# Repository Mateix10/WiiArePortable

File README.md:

# WiiArePortable

This is a work in progress custom board for a portable wii.

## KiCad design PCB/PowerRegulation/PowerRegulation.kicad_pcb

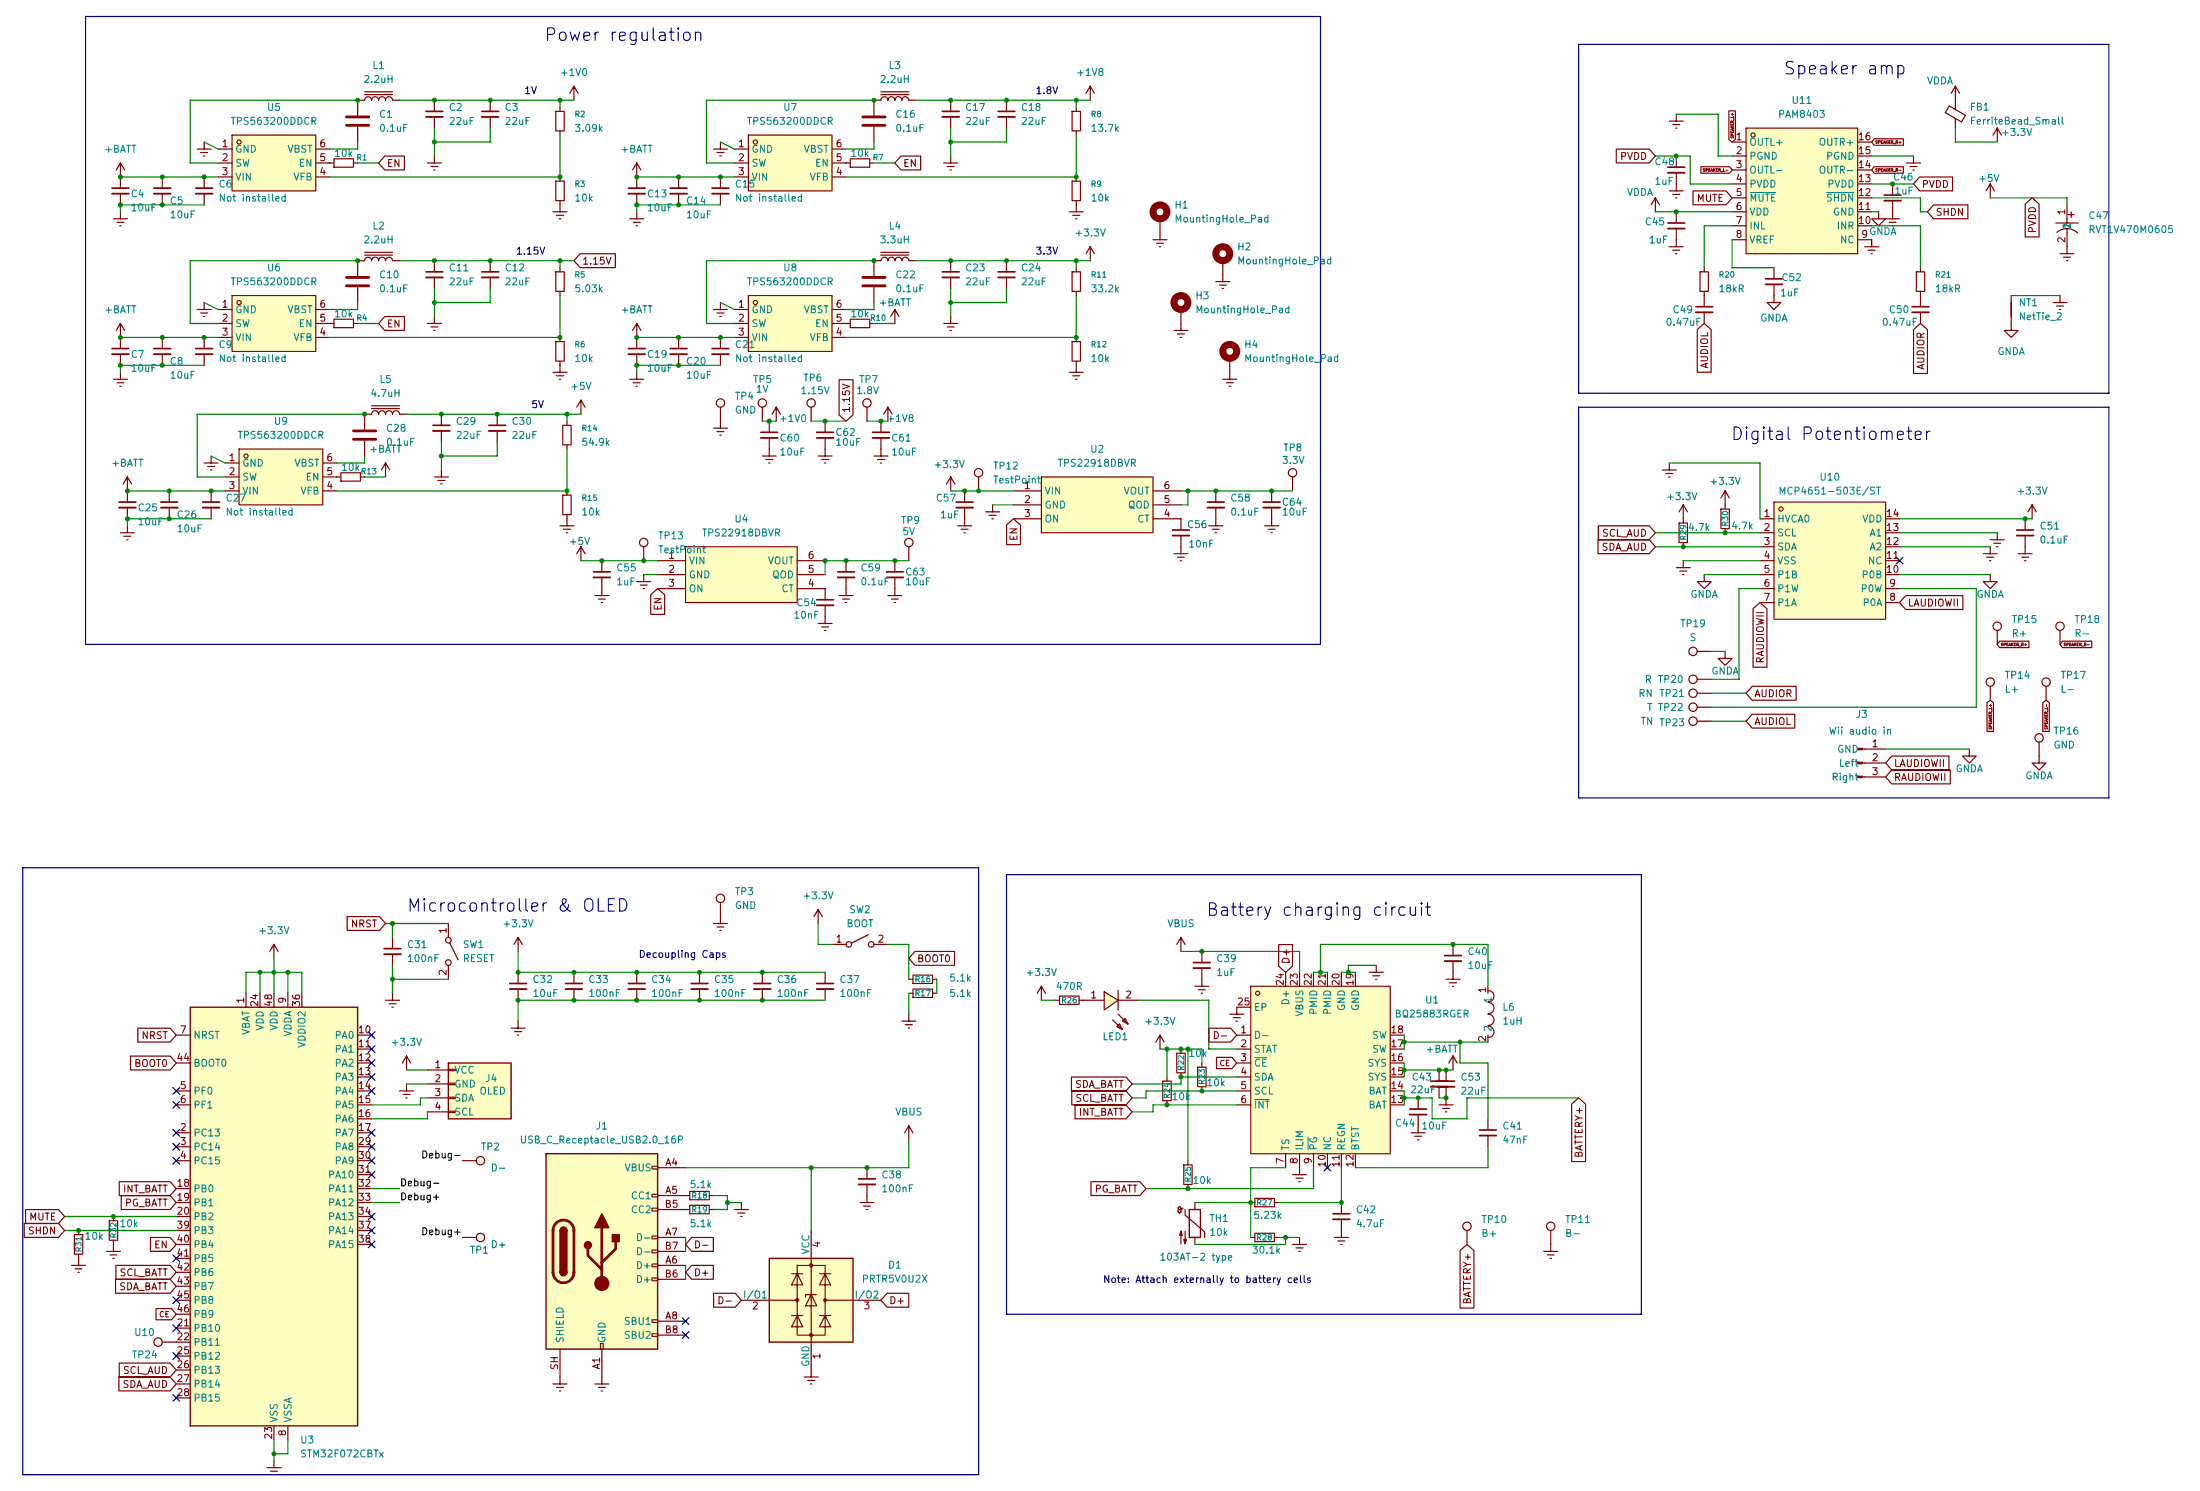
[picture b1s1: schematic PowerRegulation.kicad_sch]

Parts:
C1, C10, C16, C22, C28, C51: 0.1uF; R0603; LCSC Part C1590
C2, C3, C11, C12, C17, C18, C23, C24, C29, C30, C43, C53: 22uF; R1206; LCSC Part C5672
C4, C5, C7, C8, C13, C14, C19, C20, C25, C26, C32, C40, C44, C60, C61, C62, C63, C64: 10uF; R0805; LCSC Part C1713
C6, C9, C15, C21, C27: Not installed; R0805
C31, C33, C34, C35, C36, C37, C38: 100nF; R0603; LCSC Part C1713
C39, C45, C46, C48, C52: 1uF; R0603; LCSC Part C1592
C41: 47nF; R0603; LCSC Part C1622
C42: 4.7uF; R0805; LCSC Part C1779
C47: RVT1V470M0605; CAP-SMD_BD6.3-L6.6-W6.6-LS7.2-FD; MPN RVT1V470M0605; LCSC Part C3344
C49, C50: 0.47uF; R0603; LCSC Part C1623
C54, C56: 10nF; R1206; LCSC Part C1846
C55, C57: 1uF; R1206; LCSC Part C1848
C58, C59: 0.1uF; R1206; LCSC Part C1848
D1: PRTR5V0U2X; SOT-143; LCSC Part C5158049
FB1: FerriteBead_Small; R0805; LCSC Part C1017
H1, H2, H3, H4: MountingHole_Pad; MountingHole_3.2mm_M3_Pad_Via
J1: USB_C_Receptacle_USB2.0_16P; USB_C_Receptacle_Palconn_UTC16-G
J3: Wii audio in; PinHeader_1x03_P2.54mm_Vertical
J4: OLED; PinHeader_1x04_P2.54mm_Vertical
L1, L2, L3: 2.2uH; IND-SMD_L4.5-W4.1_SRP4020TA; LCSC Part C237985
L4: 3.3uH; IND-SMD_L5.7-W5.2; LCSC Part C189931
L5: 4.7uH; IND-SMD_L7.1-W6.6; LCSC Part C216191
L6: 1uH; IND-SMD_L5.4-W5.2_PSPMAA0503; MPN PSPMAA0503-1R0M-ANP; LCSC Part C436531
LED1: BL-HJC36G-AV-TRB; LED0603-R-RD_AMBER; MPN BL-HJC36G-AV-TRB; LCSC Part C165983
NT1: NetTie_2; NetTie-2_SMD_Pad2.0mm
R1, R3, R4, R6, R7, R9, R10, R12, R13, R15, R22, R23, R24, R25, R31, R32: 10k; R1206; LCSC Part C1489
R2: 3.09k; R0603; LCSC Part C4211
R5: 5.03k; R0603; LCSC Part C166926
R8: 13.7k; R0603; LCSC Part C22793
R11: 33.2k; R0805; LCSC Part C37252
R14: 54.9k; R0603; LCSC Part C23077
R16, R17, R18, R19: 5.1k; R0603; LCSC Part C23186
R20, R21: 18kR; R0805; LCSC Part C17506
R26: 470R; R0805; LCSC Part C436531
R27: 5.23k; R0603; LCSC Part C23068
R28: 30.1k; R1206; LCSC Part C48533691
R29, R30: 4.7k; R0805; LCSC Part C17673
SW1: RESET; SW_SPST_EVQPE1
SW2: BOOT; SW_SPST_EVQPE1
TH1: 10k; R1206; LCSC Part C1489
TP1: D+; TestPoint_Pad_D2.0mm
TP2: D-; TestPoint_Pad_D2.0mm
TP3: GND; TestPoint_Pad_D2.0mm
TP4: GND; TestPoint_Pad_D4.0mm
TP5: 1V; TestPoint_Pad_D4.0mm
TP6: 1.15V; TestPoint_Pad_D4.0mm
TP7: 1.8V; TestPoint_Pad_D4.0mm
TP8: 3.3V; TestPoint_Pad_D4.0mm
TP9: 5V; TestPoint_Pad_D4.0mm
TP10: B+; TestPoint_Pad_D4.0mm
TP11: B-; TestPoint_Pad_D4.0mm
TP12, TP13: TestPoint; TestPoint_Pad_D1.0mm
TP14: L+; TestPoint_Pad_D2.5mm
TP15: R+; TestPoint_Pad_D2.5mm
TP16: GND; TestPoint_Pad_D2.5mm
TP17: L-; TestPoint_Pad_D2.5mm
TP18: R-; TestPoint_Pad_D2.5mm
TP19: S; TestPoint_Pad_D2.0mm
TP20: R; TestPoint_Pad_D2.0mm
TP21: RN; TestPoint_Pad_D2.0mm
TP22: T; TestPoint_Pad_D2.0mm
TP23: TN; TestPoint_Pad_D2.0mm
TP24: U10; TestPoint_Pad_D2.0mm
U1: BQ25883RGER; VFQFPN-24_L4.0-W4.0-P0.50-BL-EP2.8; MPN BQ25883RGER; LCSC Part C544362
U2, U4: TPS22918DBVR; SOT-23-6_L2.9-W1.6-P0.95-LS2.8-BR; MPN TPS22918DBVR; LCSC Part C131941
U3: STM32F072CBTx; LQFP-48_L7.0-W7.0-P0.50-LS9.0-BL; LCSC Part C81720
U5, U6, U7, U8, U9: TPS563200DDCR; SOT-23-6_L2.9-W1.6-P0.95-LS2.8-BR; MPN TPS563200DDCR; LCSC Part C97253
U10: MCP4651-503E/ST; TSSOP-14_L5.0-W4.4-P0.65-LS6.4-BL; MPN MCP4651-503E/ST; LCSC Part C148010
U11: PAM8403; SOP-16_L10.0-W3.9-P1.27-LS6.0-BL; MPN PAM8403; LCSC Part C5122557

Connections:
1.15V: C11.1, C12.1, C62.1, L2.2, R5.1, TP6.1 (1_1)
+1V0: C2.1, C3.1, C60.1, L1.2, R2.1, TP5.1 (1_1)
+1V8: C17.1, C18.1, C61.1, L3.2, R8.1, TP7.1 (1_1)
+3.3V: C23.1, C24.1, C32.1, C33.1, C34.1, C35.1, C36.1, C37.1, C51.1, C57.1, FB1.2, J4.1 (VCC), L4.2, R11.1, R22.1, R23.1, R24.1, R25.1, R26.1, R29.1, R30.1, SW2.1 (A), TP12.1 (1_1), U2.1 (VIN), U3.1 (VBAT), U3.9 (VDDA), U3.24 (VDD), U3.36 (VDDIO2), U3.48 (VDD), U10.14 (VDD)
+BATT: C4.1, C5.1, C6.1, C7.1, C8.1, C9.1, C13.1, C14.1, C15.1, C19.1, C20.1, C21.1, C25.1, C26.1, C27.1, C43.1, C53.1, R10.2, R13.2, U1.15 (SYS), U1.16 (SYS), U5.3 (VIN), U6.3 (VIN), U7.3 (VIN), U8.3 (VIN), U9.3 (VIN)
/Debug+: TP1.1 (1_1), U3.33 (PA12)
/Debug-: TP2.1 (1_1), U3.32 (PA11)
AUDIOL: C49.2, TP23.1 (1_1)
AUDIOR: C50.2, TP21.1 (1_1)
BATTERY+: C44.1, TP10.1 (1_1), U1.13 (BAT), U1.14 (BAT)
BOOT0: R16.1, SW2.2 (B), U3.44 (BOOT0)
CE: U1.3 (~CE), U3.46 (PB9)
D+: D1.3 (I/O2), J1.A6 (D+), J1.B6 (D+), U1.24 (D+)
D-: D1.2 (I/O1), J1.A7 (D-), J1.B7 (D-), U1.1 (D-)
EN: R1.2, R4.2, R7.2, U2.3 (ON), U3.40 (PB4), U4.3 (ON)
GNDA: C52.2, J3.1 (GND), NT1.1, TP16.1 (1_1), TP19.1 (1_1), U10.5 (P1B), U10.10 (P0B), U11.11 (GND)
GNDREF: C2.2, C3.2, C4.2, C5.2, C6.2, C7.2, C8.2, C9.2, C11.2, C12.2, C13.2, C14.2, C15.2, C17.2, C18.2, C19.2, C20.2, C21.2, C23.2, C24.2, C25.2, C26.2, C27.2, C29.2, C30.2, C31.2, C32.2, C33.2, C34.2, C35.2, C36.2, C37.2, C38.2, C39.2, C40.2, C42.2, C43.2, C44.2, C45.2, C46.2, C47.2, C48.2, C51.2, C53.2, C54.2, C55.2, C56.2, C57.2, C58.2, C59.2, C60.2, C61.2, C62.2, C63.2, C64.2, D1.1 (GND), H1.1 (1_1), H2.1 (1_1), H3.1 (1_1), H4.1 (1_1), J1.A1 (GND), J1.A12 (GND), J1.B1 (GND), J1.B12 (GND), J1.SH (SHIELD), J4.2 (GND), NT1.2, R3.2, R6.2, R9.2, R12.2, R15.2, R17.1, R18.2, R19.2, R28.2, R31.2, R32.2, SW1.2 (B), TH1.2, TP3.1 (1_1), TP4.1 (1_1), TP11.1 (1_1), U1.8 (ILIM), U1.19 (GND), U1.20 (GND), U1.25 (EP), U2.2 (GND), U3.8 (VSSA), U3.23 (VSS), U3.35 (VSS), U3.47 (VSS), U4.2 (GND), U5.1 (GND), U6.1 (GND), U7.1 (GND), U8.1 (GND), U9.1 (GND), U10.1 (HVCA0), U10.4 (VSS), U10.12 (A2), U10.13 (A1), U11.2 (PGND), U11.9 (NC), U11.15 (PGND)
INT_BATT: R24.2, U1.6 (~INT), U3.18 (PB0)
LAUDIOWII: J3.2 (Left), U10.8 (P0A)
MUTE: R32.1, U3.20 (PB2), U11.5 (~MUTE)
NRST: C31.1, SW1.1 (A), U3.7 (NRST)
unnamed: C40.1, L6.1, U1.21 (PMID), U1.22 (PMID)
unnamed: C41.1, L6.2, U1.17 (SW), U1.18 (SW)
unnamed: C49.1, R20.2
unnamed: C50.1, R21.2
unnamed: J1.A5 (CC1), R18.1
unnamed: J1.B5 (CC2), R19.1
unnamed: J4.4 (SCL), U3.16 (PA6)
unnamed: J4.3 (SDA), U3.15 (PA5)
unnamed: LED1.1 (A), R26.2
unnamed: LED1.2 (C), U1.2 (STAT)
unnamed: R16.2, R17.2
unnamed: C41.2, U1.12 (BTST)
unnamed: C42.1, R27.2, U1.11 (REGN)
unnamed: R27.1, R28.1, TH1.1, U1.7 (TS)
unnamed: C56.1, U2.4 (CT)
unnamed: C58.1, C64.1, TP8.1 (1_1), U2.5 (QOD), U2.6 (VOUT)
unnamed: TP24.1 (1_1), U3.22 (PB11)
unnamed: C54.1, U4.4 (CT)
unnamed: C59.1, C63.1, TP9.1 (1_1), U4.5 (QOD), U4.6 (VOUT)
unnamed: R1.1, U5.5 (EN)
unnamed: C1.1, L1.1, U5.2 (SW)
unnamed: C1.2, U5.6 (VBST)
unnamed: R2.2, R3.1, U5.4 (VFB)
unnamed: R4.1, U6.5 (EN)
unnamed: C10.1, L2.1, U6.2 (SW)
unnamed: C10.2, U6.6 (VBST)
unnamed: R5.2, R6.1, U6.4 (VFB)
unnamed: R7.1, U7.5 (EN)
unnamed: C16.1, L3.1, U7.2 (SW)
unnamed: C16.2, U7.6 (VBST)
unnamed: R8.2, R9.1, U7.4 (VFB)
unnamed: R10.1, U8.5 (EN)
unnamed: C22.1, L4.1, U8.2 (SW)
unnamed: C22.2, U8.6 (VBST)
unnamed: R11.2, R12.1, U8.4 (VFB)
unnamed: R13.1, U9.5 (EN)
unnamed: C28.1, L5.1, U9.2 (SW)
unnamed: C28.2, U9.6 (VBST)
unnamed: R14.2, R15.1, U9.4 (VFB)
unnamed: TP22.1 (1_1), U10.9 (P0W)
unnamed: TP20.1 (1_1), U10.6 (P1W)
unnamed: R20.1, U11.7 (INL)
unnamed: R21.1, U11.10 (INR)
unnamed: C52.1, U11.8 (VREF)
PG_BATT: R25.2, U1.9 (~PG), U3.19 (PB1)
PVDD: C29.1, C30.1, C46.1, C47.1, C48.1, C55.1, L5.2, R14.1, TP13.1 (1_1), U4.1 (VIN), U11.4 (PVDD), U11.13 (PVDD)
RAUDIOWII: J3.3 (Right), U10.7 (P1A)
SCL_AUD: R30.2, U3.26 (PB13), U10.2 (SCL)
SCL_BATT: R23.2, U1.5 (SCL), U3.42 (PB6)
SDA_AUD: R29.2, U3.27 (PB14), U10.3 (SDA)
SDA_BATT: R22.2, U1.4 (SDA), U3.43 (PB7)
SHDN: R31.1, U3.39 (PB3), U11.12 (~SHDN)
SPEAKER_L+: TP14.1 (1_1), U11.1 (OUTL+)
SPEAKER_L-: TP17.1 (1_1), U11.3 (OUTL-)
SPEAKER_R+: TP15.1 (1_1), U11.16 (OUTR+)
SPEAKER_R-: TP18.1 (1_1), U11.14 (OUTR-)
VBUS: C38.1, C39.1, D1.4 (VCC), J1.A4 (VBUS), J1.A9 (VBUS), J1.B4 (VBUS), J1.B9 (VBUS), U1.23 (VBUS)
VDDA: C45.1, FB1.1, U11.6 (VDD)

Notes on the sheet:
Digital Potentiometer
3.3V
Decoupling Caps
Note: Attach externally to battery cells
1.8V
Microcontroller & OLED
Power regulation
Battery charging circuit
1.15V
Speaker amp

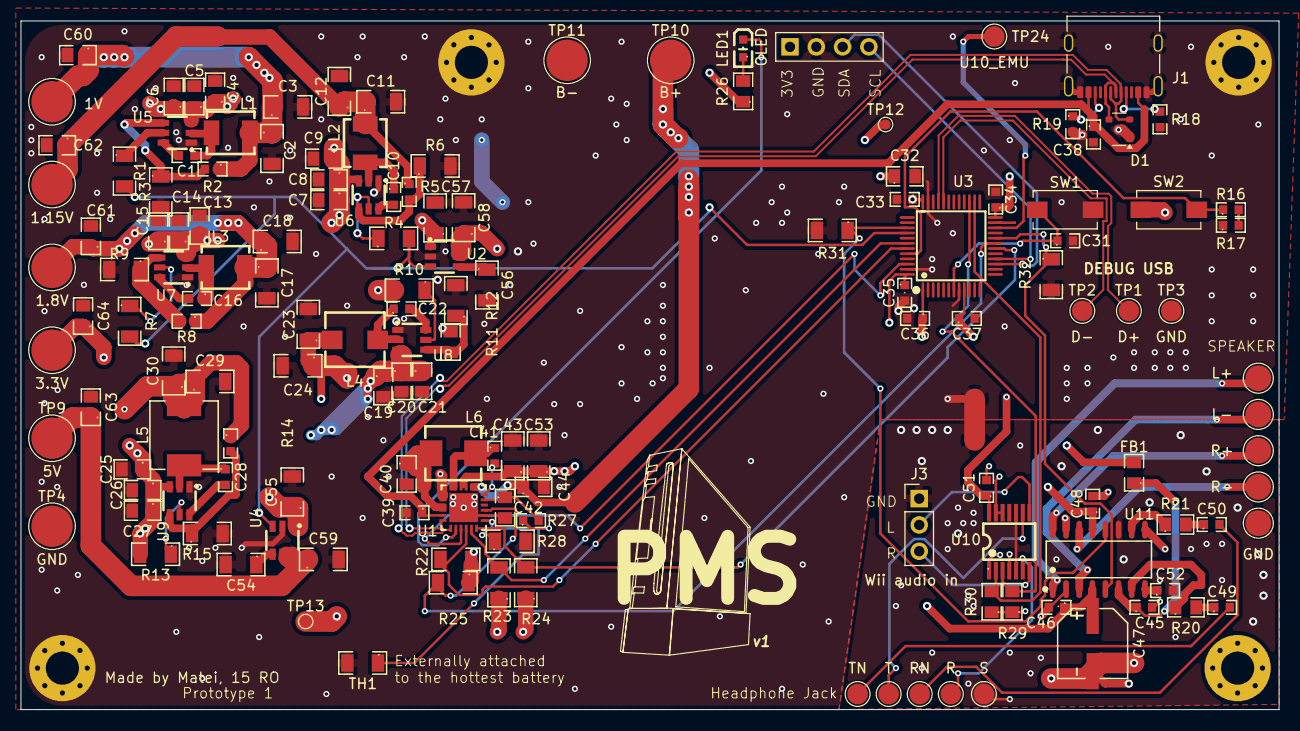
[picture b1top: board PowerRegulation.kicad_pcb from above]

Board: 4 copper layers, 121.5 x 66.5 mm, 151 parts (0 on the bottom side), 79 nets.

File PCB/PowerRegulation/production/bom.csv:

Designator,Footprint,Quantity,Value,LCSC Part #
"C1, C10, C16, C22, C28, C51",R0603,6,0.1uF,C22793
"C11, C12, C17, C18, C2, C23, C24, C29, C3, C30, C43, C53",R1206,12,22uF,C1489
"C13, C14, C19, C20, C25, C26, C32, C4, C40, C44, C5, C60, C61, C62, C63, C64, C7, C8",R0805,18,10uF,C37252
"C15, C21, C27, C6, C9",R0805,5,Not installed,C37252
"C31, C33, C34, C35, C36, C37, C38",R0603,7,100nF,C22793
"C39, C45, C46, C48, C52",R0603,5,1uF,C22793
C41,R0603,1,47nF,C22793
C42,R0805,1,4.7uF,C37252
C47,CAP-SMD_BD6.3-L6.6-W6.6-LS7.2-FD,1,RVT1V470M0605,C3344
"C49, C50",R0603,2,0.47uF,C22793
"C54, C56",R1206,2,10nF,C1489
"C55, C57",R1206,2,1uF,C1489
"C58, C59",R1206,2,0.1uF,C1489
D1,SOT-143,1,PRTR5V0U2X,
FB1,R0805,1,FerriteBead_Small,C37252
J1,USB_C_Receptacle_Palconn_UTC16-G,1,USB_C_Receptacle_USB2.0_16P,
J3,PinHeader_1x03_P2.54mm_Vertical,1,Wii audio in,
J4,PinHeader_1x04_P2.54mm_Vertical,1,OLED,
"L1, L2, L3",IND-SMD_L4.5-W4.1_SRP4020TA,3,2.2uH,C237985
L4,IND-SMD_L5.7-W5.2,1,3.3uH,C189931
L5,IND-SMD_L7.1-W6.6,1,4.7uH,C216191
L6,IND-SMD_L5.4-W5.2_PSPMAA0503,1,1uH,C436531
LED1,LED0603-R-RD_AMBER,1,BL-HJC36G-AV-TRB,C165983
"R1, R10, R12, R13, R15, R22, R23, R24, R25, R3, R31, R32, R4, R6, R7, R9, TH1",R1206,17,10k,C1489
R11,R0805,1,33.2k,C37252
R14,R0603,1,54.9k,C22793
"R16, R17, R18, R19",R0603,4,5.1k,C22793
R2,R0603,1,3.09k,C22793
"R20, R21",R0805,2,18kR,C37252
R26,R0805,1,470R,C37252
R27,R0603,1,5.23k,C22793
R28,R1206,1,30.1k,C1489
"R29, R30",R0805,2,4.7k,C37252
R5,R0603,1,5.03k,C22793
R8,R0603,1,13.7k,C22793
SW1,SW_SPST_EVQPE1,1,RESET,
SW2,SW_SPST_EVQPE1,1,BOOT,
TP1,TestPoint_Pad_D2.0mm,1,D+,
TP10,TestPoint_Pad_D4.0mm,1,B+,
TP11,TestPoint_Pad_D4.0mm,1,B-,
"TP12, TP13",TestPoint_Pad_D1.0mm,2,TestPoint,
TP14,TestPoint_Pad_D2.5mm,1,L+,
TP15,TestPoint_Pad_D2.5mm,1,R+,
TP16,TestPoint_Pad_D2.5mm,1,GND,
TP17,TestPoint_Pad_D2.5mm,1,L-,
TP18,TestPoint_Pad_D2.5mm,1,R-,
TP19,TestPoint_Pad_D2.0mm,1,S,
TP2,TestPoint_Pad_D2.0mm,1,D-,
TP20,TestPoint_Pad_D2.0mm,1,R,
TP21,TestPoint_Pad_D2.0mm,1,RN,
TP22,TestPoint_Pad_D2.0mm,1,T,
TP23,TestPoint_Pad_D2.0mm,1,TN,
TP3,TestPoint_Pad_D2.0mm,1,GND,
TP4,TestPoint_Pad_D4.0mm,1,GND,
TP5,TestPoint_Pad_D4.0mm,1,1V,
TP6,TestPoint_Pad_D4.0mm,1,1.15V,
TP7,TestPoint_Pad_D4.0mm,1,1.8V,
TP8,TestPoint_Pad_D4.0mm,1,3.3V,
TP9,TestPoint_Pad_D4.0mm,1,5V,
U1,VFQFPN-24_L4.0-W4.0-P0.50-BL-EP2.8,1,BQ25883RGER,C544362
U10,TSSOP-14_L5.0-W4.4-P0.65-LS6.4-BL,1,MCP4651-503E/ST,C148010
U11,SOP-16_L10.0-W3.9-P1.27-LS6.0-BL,1,PAM8403,C5122557
"U2, U4",SOT-23-6_L2.9-W1.6-P0.95-LS2.8-BR,2,TPS22918DBVR,C131941
U3,LQFP-48_L7.0-W7.0-P0.50-LS9.0-BL,1,STM32F072CBTx,C81720
"U5, U6, U7, U8, U9",SOT-23-6_L2.9-W1.6-P0.95-LS2.8-BR,5,TPS563200DDCR,C97253

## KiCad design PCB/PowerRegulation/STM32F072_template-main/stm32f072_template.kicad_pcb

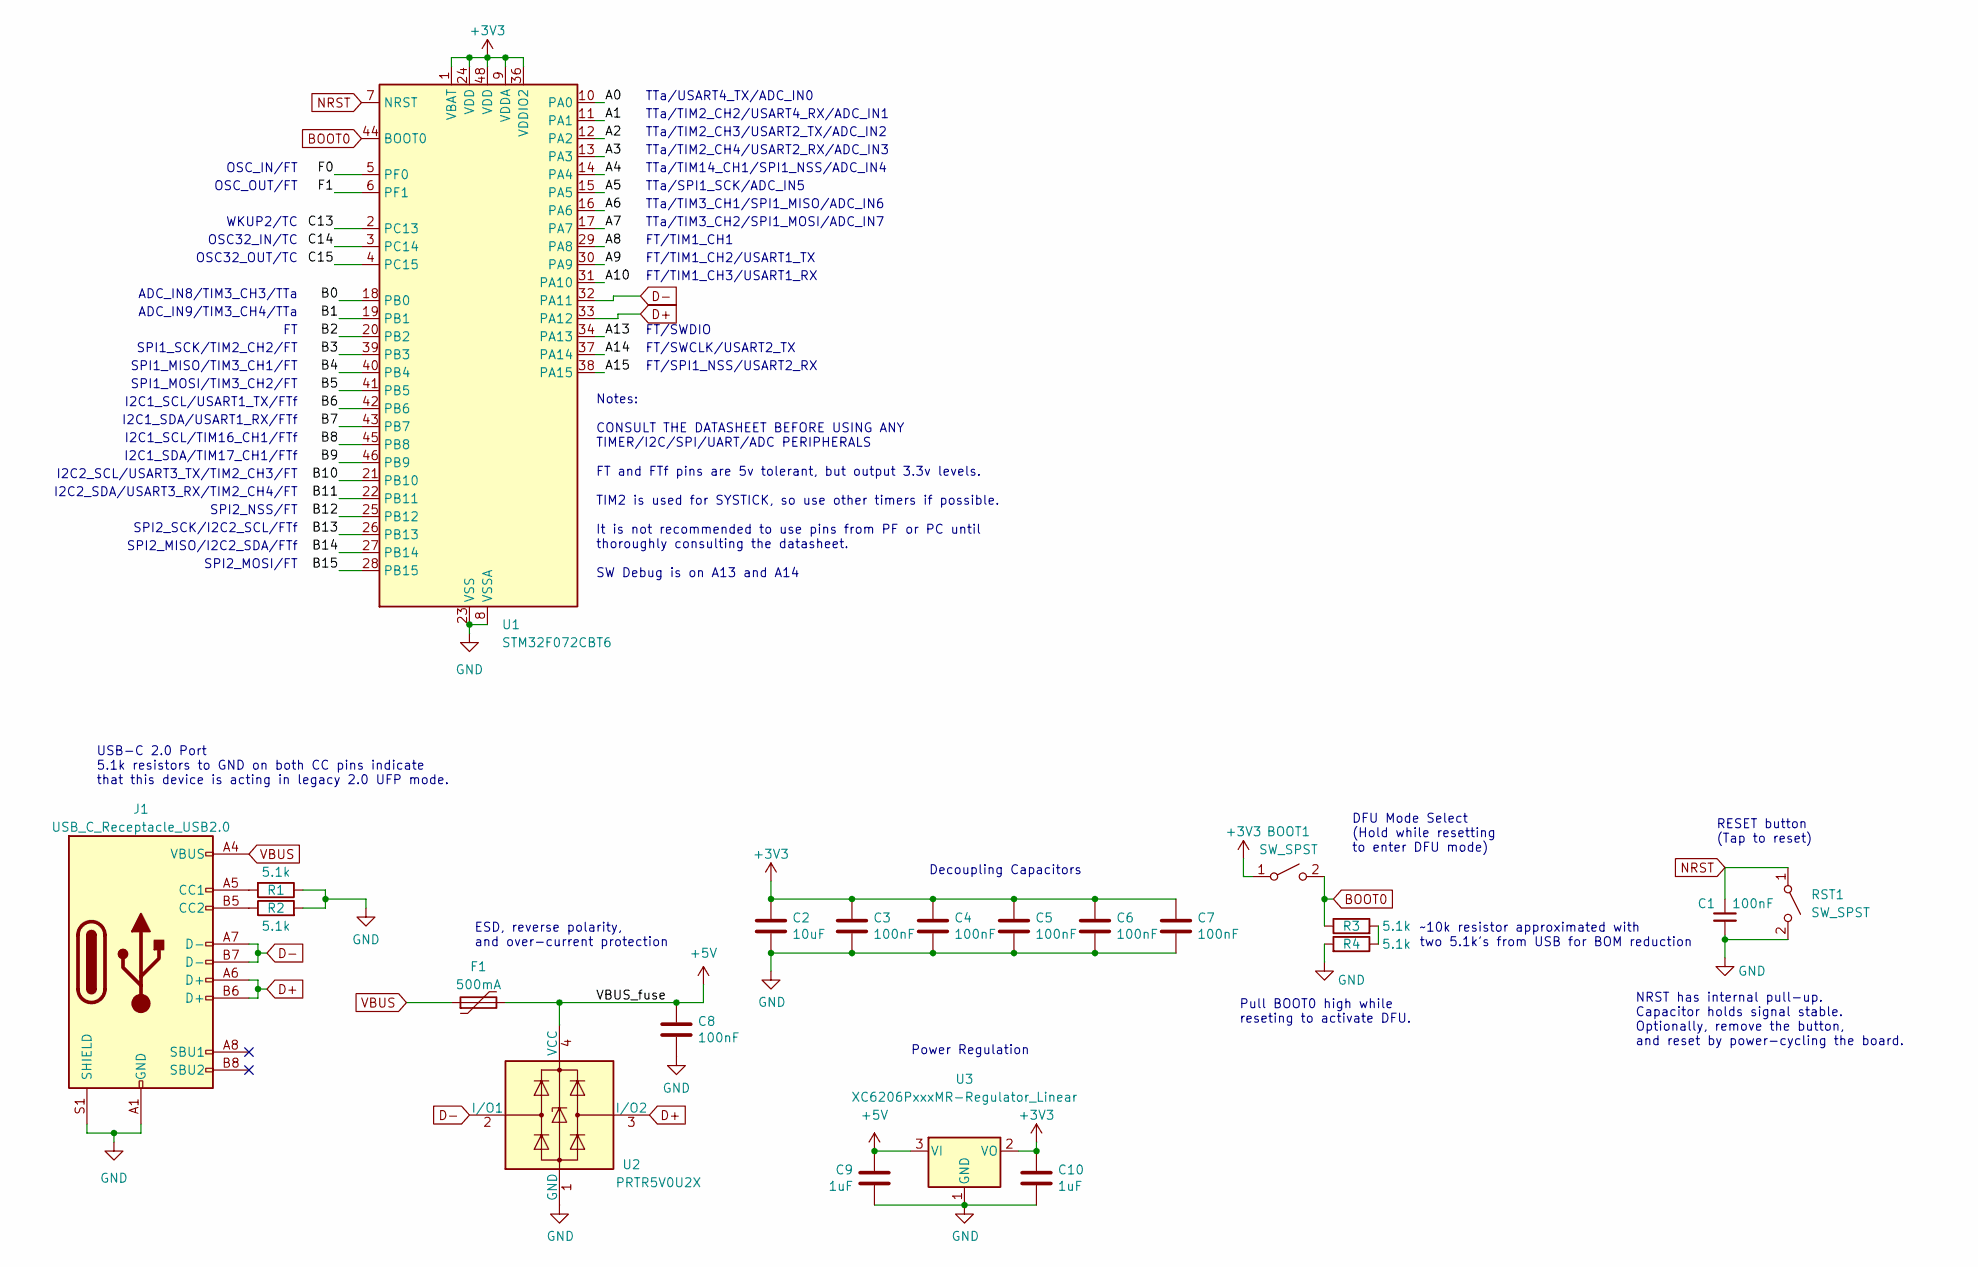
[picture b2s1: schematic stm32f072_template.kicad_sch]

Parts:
BOOT1: SW_SPST; SW_SPST_TL3342
C1, C3, C4, C5, C6, C7, C8: 100nF; C_0402_1005Metric; LCSC C307331
C2: 10uF; C_0603_1608Metric; LCSC C307331
C9, C10: 1uF; C_0402_1005Metric; LCSC C307331
F1: 500mA; Fuse_1206_3216Metric; LCSC C135341
J1: USB_C_Receptacle_USB2.0; USB_C_Receptacle_HRO_TYPE-C-31-M-12; JlcRotOffset 180
R1, R2, R3, R4: 5.1k; R_0402_1005Metric
RST1: SW_SPST; SW_SPST_TL3342
U1: STM32F072CBT6; LQFP-48_7x7mm_P0.5mm; JlcRotOffset 90
U2: PRTR5V0U2X; SOT-143; LCSC C2827688
U3: XC6206PxxxMR-Regulator_Linear; SOT-23; LCSC C5446

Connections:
+3V3: BOOT1.1 (A), C2.1, C3.1, C4.1, C5.1, C6.1, C7.1, C10.1, U1.1 (VBAT), U1.9 (VDDA), U1.24 (VDD), U1.36 (VDDIO2), U1.48 (VDD), U3.2 (VO); also elsewhere on the board
+5V: C8.1, C9.1, F1.2, U2.4 (VCC), U3.3 (VI)
/A0: U1.10 (PA0); also elsewhere on the board
/A1: U1.11 (PA1); also elsewhere on the board
/A2: U1.12 (PA2); also elsewhere on the board
/A3: U1.13 (PA3); also elsewhere on the board
/A4: U1.14 (PA4); also elsewhere on the board
/A5: U1.15 (PA5); also elsewhere on the board
/A6: U1.16 (PA6); also elsewhere on the board
/A7: U1.17 (PA7); also elsewhere on the board
/A8: U1.29 (PA8); also elsewhere on the board
/A9: U1.30 (PA9); also elsewhere on the board
/A10: U1.31 (PA10); also elsewhere on the board
/A13: U1.34 (PA13); also elsewhere on the board
/A14: U1.37 (PA14); also elsewhere on the board
/A15: U1.38 (PA15); also elsewhere on the board
/B0: U1.18 (PB0); also elsewhere on the board
/B1: U1.19 (PB1); also elsewhere on the board
/B2: U1.20 (PB2); also elsewhere on the board
/B3: U1.39 (PB3); also elsewhere on the board
/B4: U1.40 (PB4); also elsewhere on the board
/B5: U1.41 (PB5); also elsewhere on the board
/B6: U1.42 (PB6); also elsewhere on the board
/B7: U1.43 (PB7); also elsewhere on the board
/B8: U1.45 (PB8); also elsewhere on the board
/B9: U1.46 (PB9); also elsewhere on the board
/B10: U1.21 (PB10); also elsewhere on the board
/B11: U1.22 (PB11); also elsewhere on the board
/B12: U1.25 (PB12); also elsewhere on the board
/B13: U1.26 (PB13); also elsewhere on the board
/B14: U1.27 (PB14); also elsewhere on the board
/B15: U1.28 (PB15); also elsewhere on the board
/C13: U1.2 (PC13); also elsewhere on the board
/C14: U1.3 (PC14); also elsewhere on the board
/C15: U1.4 (PC15); also elsewhere on the board
/F0: U1.5 (PF0); also elsewhere on the board
/F1: U1.6 (PF1); also elsewhere on the board
BOOT0: BOOT1.2 (B), R3.1, U1.44 (BOOT0); also elsewhere on the board
GND: C1.2, C2.2, C3.2, C4.2, C5.2, C6.2, C7.2, C8.2, C9.2, C10.2, J1.A1 (GND), J1.A12 (GND), J1.B1 (GND), J1.B12 (GND), J1.S1 (SHIELD), R1.1, R2.2, R4.2, RST1.2 (B), U1.8 (VSSA), U1.23 (VSS), U1.35 (VSS), U1.47 (VSS), U2.1 (GND), U3.1 (GND); also elsewhere on the board
NRST: C1.1, RST1.1 (A), U1.7 (NRST); also elsewhere on the board
unnamed: J1.A5 (CC1), R1.2
unnamed: J1.B5 (CC2), R2.1
unnamed: R3.2, R4.1
VBUS: F1.1, J1.A4 (VBUS), J1.A9 (VBUS), J1.B4 (VBUS), J1.B9 (VBUS); also elsewhere on the board

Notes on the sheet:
SPI1_SCK/TIM2_CH2/FT
FT/TIM1_CH1
FT/TIM1_CH3/USART1_RX
SPI2_NSS/FT
Notes: CONSULT THE DATASHEET BEFORE USING ANY TIMER/I2C/SPI/UART/ADC PERIPHERALS FT and FTf pins are 5v tolerant, but output 3.3v levels. TIM2 is used for SYSTICK, so use other timers if possible. It is not recommended to use pins from PF or PC until thoroughly consulting the datasheet. SW Debug is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
TTa/TIM2_CH4/USART2_RX/ADC_IN3
NRST has internal pull-up. Capacitor holds signal stable. Optionally, remove the button, and reset by power-cycling the board.
FT/SWDIO
Decoupling Capacitors
SPI1_MOSI/TIM3_CH2/FT
ADC_IN9/TIM3_CH4/TTa
I2C2_SCL/USART3_TX/TIM2_CH3/FT
SPI2_MISO/I2C2_SDA/FTf
FT/SWCLK/USART2_TX
I2C1_SCL/TIM16_CH1/FTf
~10k resistor approximated with two 5.1k's from USB for BOM reduction
TTa/TIM2_CH2/USART4_RX/ADC_IN1
USB-C 2.0 Port 5.1k resistors to GND on both CC pins indicate that this device is acting in legacy 2.0 UFP mode.
TTa/TIM2_CH3/USART2_TX/ADC_IN2
OSC_IN/FT
DFU Mode Select (Hold while resetting to enter DFU mode)
WKUP2/TC
I2C2_SDA/USART3_RX/TIM2_CH4/FT
ADC_IN8/TIM3_CH3/TTa
RESET button (Tap to reset)
Pull BOOT0 high while reseting to activate DFU.
I2C1_SDA/TIM17_CH1/FTf
TTa/SPI1_SCK/ADC_IN5
TTa/TIM3_CH1/SPI1_MISO/ADC_IN6
TTa/TIM3_CH2/SPI1_MOSI/ADC_IN7
OSC32_OUT/TC
FT/SPI1_NSS/USART2_RX
SPI1_MISO/TIM3_CH1/FT
OSC32_IN/TC
TTa/TIM14_CH1/SPI1_NSS/ADC_IN4
I2C1_SDA/USART1_RX/FTf
SPI2_MOSI/FT
FT/TIM1_CH2/USART1_TX
Power Regulation
SPI2_SCK/I2C2_SCL/FTf

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
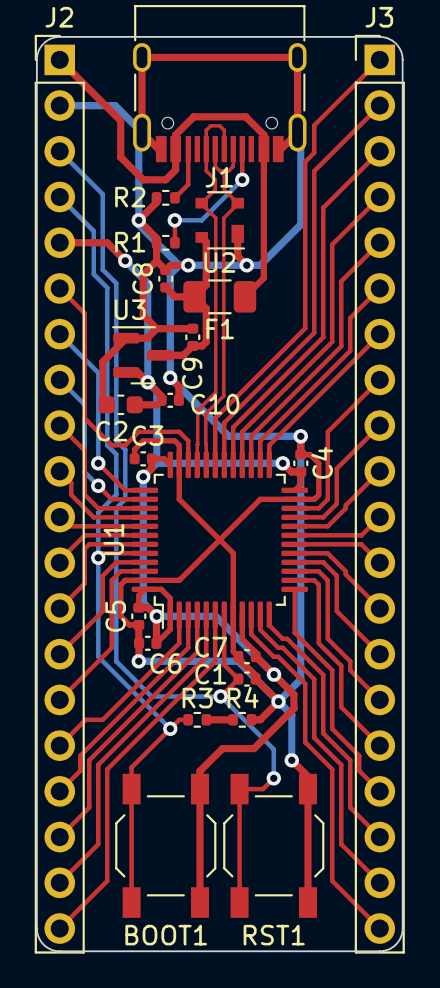
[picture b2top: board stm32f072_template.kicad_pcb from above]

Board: 2 copper layers, 20.3 x 50.8 mm, 23 parts (0 on the bottom side), 46 nets.

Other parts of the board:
J2, J3: Conn_01x20; PinHeader_1x20_P2.54mm_Vertical

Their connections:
+3V3: J2.5; also elsewhere on the board
/A0: J3.20; also elsewhere on the board
/A1: J3.19; also elsewhere on the board
/A2: J3.18; also elsewhere on the board
/A3: J3.17; also elsewhere on the board
/A4: J3.16; also elsewhere on the board
/A5: J3.15; also elsewhere on the board
/A6: J3.14; also elsewhere on the board
/A7: J3.13; also elsewhere on the board
/A8: J3.3; also elsewhere on the board
/A9: J3.2; also elsewhere on the board
/A10: J3.1; also elsewhere on the board
/A13: J2.6; also elsewhere on the board
/A14: J2.7; also elsewhere on the board
/A15: J2.8; also elsewhere on the board
/B0: J3.12; also elsewhere on the board
/B1: J3.11; also elsewhere on the board
/B2: J3.10; also elsewhere on the board
/B3: J2.9; also elsewhere on the board
/B4: J2.10; also elsewhere on the board
/B5: J2.11; also elsewhere on the board
/B6: J2.12; also elsewhere on the board
/B7: J2.13; also elsewhere on the board
/B8: J2.14; also elsewhere on the board
/B9: J2.15; also elsewhere on the board
/B10: J3.9; also elsewhere on the board
/B11: J3.8; also elsewhere on the board
/B12: J3.7; also elsewhere on the board
/B13: J3.6; also elsewhere on the board
/B14: J3.5; also elsewhere on the board
/B15: J3.4; also elsewhere on the board
/C13: J2.16; also elsewhere on the board
/C14: J2.17; also elsewhere on the board
/C15: J2.18; also elsewhere on the board
/F0: J2.19; also elsewhere on the board
/F1: J2.20; also elsewhere on the board
BOOT0: J2.4; also elsewhere on the board
GND: J2.2; also elsewhere on the board
NRST: J2.3; also elsewhere on the board
VBUS: J2.1; also elsewhere on the board
